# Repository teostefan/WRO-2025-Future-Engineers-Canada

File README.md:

# WRO-2025-Future-Engineers-Canada

The following repository contains the code and technical documentation regarding
the robot created by the CarletonU-uOttawa joint team for the 2025 WRO Future
Engineers competition.

## Contents

- [About our Team](https://github.com/teostefan/WRO-2025-Future-Engineers-Canada/blob/main/README.md#about-our-team)
- [Demo Video](https://github.com/teostefan/WRO-2025-Future-Engineers-Canada/blob/main/README.md#demo-video)
- [Software Setup](https://github.com/teostefan/WRO-2025-Future-Engineers-Canada/blob/main/README.md#software-setup)
- [Power and Sensor Management](https://github.com/teostefan/WRO-2025-Future-Engineers-Canada/blob/main/README.md#power-and-sensor-management)
- [Obstacle Management](https://github.com/teostefan/WRO-2025-Future-Engineers-Canada/blob/main/README.md#obstacle-management)
- [Mobility Management](https://github.com/teostefan/WRO-2025-Future-Engineers-Canada/blob/main/README.md#mobility-management)

## About our Team

Oscar Barbieri is a student at the University of Ottawa and is studying software engineering, and Stefan Teodorescu is a student a Carleton University studying aerospace avionics. Last year, Oscar and Stefan participated in the WRO Future Innovators challenge and made it into the international finals in İzmir. This year, both students have decided to participate in the WRO Future Engineers competition as a means to further their knowledge regarding mechatronics and systems programming.

## Demo Video

A demonstration video of our robot performing both challenges can be found in the [```video``` directory](https://github.com/teostefan/WRO-2025-Future-Engineers-Canada/tree/main/video).

## Software Setup

### Compiling and Running the Robot's Firmware (Linux)

To get started, clone the repository and build the firmware using `make`:

```sh
git clone https://github.com/teostefan/WRO-2025-Future-Engineers-Beta.git
cd WRO-2025-Future-Engineers-Beta
make
```

> **Note**: Depending on how your Linux system is configured, an "insufficient
> privileges" error may be thrown on compilation regarding the file
> `kf_matrix_gen.sh`. To solve this, run
> `sudo chmod 777 ./software/kf/kf_matrix_gen.sh` in the repository's root. If
> this error still persists, use `sudo` in front of `make` as your user might
> not have enough privileges to execute the above bash file.

Then, simply run the `main` executable in the generated `builds` folder:

```sh
builds/main
```

### Compiling and Running Individual Tests

To generate the test executables, run:

```sh
make all-tests
```

Afterwards, all tests will be in the `builds` folder and have a name in the
format `test_xx`. Each test can then be individually executed as in the
following example:

```sh
builds/test_cv
```

### Software Dependencies

If running on Linux, all of the below dependencies should be pre-installed.

- `ffmpeg` - Abstraction layer for the driver, also used for applying filters to
  the video feed.
- `v4l2` - Video4Linux2 multimedia drivers.
- `ffplay` - Media player GUI for debugging.
- `unistd.h` - The UNIX standard header.

## Power and Sensor Management

||
|:--:|
|*Figure 1: Annotated diagram of the vehicle. Individual components are discussed in the subsequent sections.*|

This section pertains to the electrical engineering aspects of our vehicle. Design choices such as computing platforms, power supplies, sensors and motor controllers are discussed. The majority of peripherals have been purchased as breakout boards, and a custom Raspberry-P "Hat" acts as a distribution box and motor controller. A general block diagram of the robot's electrical systems is provided below.

||
|:--:|
|*Figure 2: Diagram of the vehicle's electrical systems. Schematics regarding the custom Raspberry Pi Hat PCB and 5V converter for the servo are provided in the sections below.*|

### Computing Platform

The main controller for the robot is a Raspberry Pi 4B Single Board Computer (SBC). All processing is done on this platform, and no additional controllers have been used, except for an ATTINY45 that generates Pulse-Width Modulation (PWM) to control the speed on the driving motor. This ensures that the system remains simple and allows for a smaller vehicle, which implies better manoeuvrability. The Raspberry-Pi model 4B was specifically chosen as it has a good amount of processing capabilities for the computer-vision algorithms and does not excessively consume power like the newer model 5 (~2.5A@5V versus 5A@5V).

### Power Supply

The vehicle is powered by a 2Ah lithium-ion battery pack that feeds 7.4V nominal into a 3.4A fixed 5V buck regulator and a variable 2A buck-boost regulator set to approximately 9V. The 5V regulator supplies the Raspberry Pi, while the 9V regulator supplies the driving motor. As the steering servo requires 5V only, the 9V from the motor power supply is stepped down to 5V via a simple LM7805 linear regulator circuit (see Figure 3). Although the 5V could have been supplied from the main 5V regulator, this would have been undesirable as any electrical noise caused by the servomotor could permeate to the Raspberry Pi and cause instabilities. For supplying the sensors which work at 3.3V, the internal regulator on the Raspberry Pi is used.

||
|:--:|
|*Figure 3: Schematic of the LM7805 5V regulator for the steering servo. Production files for this board can be found in the [`pcb/servo_regulator`](https://github.com/teostefan/WRO-2025-Future-Engineers-Canada/tree/main/pcb/servo_regulator) directory.*|

||
|:--:|
|*Figure 4: Rendering of the servo regulator custom PCB in KiCAD.*|

### Sensor and Motor Management

In addition to the camera for obstacle detection, as many sensors as possible have been installed on the robot to simplify the control algorithms and to avoid estimating data. For example, all four sides of the robot have optical Time-of-Flight (ToF) distance sensors, allowing the vehicle not only to determine it's rectilinear position, but also to measure clearances precisely for manoeuvres such as parallel parking. In addition, a gyroscope has been installed which can measure absolute rotation angles of the robot. The gyro sensor is also used in a proportional controller to keep the robot driving straight when required.

All sensors, except for the camera which is connected via USB, are interfaced via a common I²C bus. To prevent conflicts in between sensors which have the same addresses (the 4 ToF sensors), an I²C-controlled multiplexer is used for connecting the main bus to only one sensor at a time.

Also on this main I²C bus is an ATTINY45 which is configured as a slave. It generates PWM signals that are then used to drive the DC driving motor via an H-bridge at varying speeds in forwards or reverse. The steering servomotor is separate and is controlled directly by the Raspberry Pi through PWM.

In order to reduce the number of external components and keep the wiring relatively manageable, a custom Raspberry Pi "Hat" has been designed. It includes connectors for all of the individual peripherals and integrates the driving motor controller as well as the I²C multiplexer. The circuit board was designed in KiCAD and all relevant files can be found in the `pcb/main` directory. See Figure 5 at the end of this page for the main board's schematic, and the green inset in Figure 2 for the main board's block diagram.

#### I²C Peripheral Mapping

**Note:** All I²C peripherals are on I²C channel 1 (GPIO2/SDA & GPIO3/SCL).

| Peripheral | Description | I²C Address | Related Drivers |
| ---------- | ----------- | ----------- | --------------- |
| ESC        | Electronic speed controller for main motor. It is just an ATTNY25/45 programmed with the firmware contained in the `software/esc/esc.ino` C++ file. GPIO23 is also used by the driver to put this peripheral to sleep. | `0x08` | `software/esc` |
| BNO055     | Gyroscope/IMU. By default, the address of this sensor will be `0x29`, but this will interfere with the ToF sensors. To select the alternate address `0x28`, pull the `ADC` pin on the breakout board low. | `0x28` | `software/gyro` |
| VL53L0X    | One of four laser ToF sensors. As all sensors have the same address, they must be selected via the I²C switch (see next row). | `0x29` | `software/tof` |
| TCA9544    | 4 Channel I²C switch / multiplexer for selecting 1 of 4 VL53L0X sensors. | `0x70` | `software/i2cmux` |

#### Non-I²C Peripheral Mapping

|   Peripheral   | Description | Pin number & GPIO | Related Drivers |
| -------------- | ----------- | ----------- | --------------- |
| SG-5010        | Standard RC PWM-controlled servo for steering. | `GPIO13/PIN33/PWM1` | `software/esc` |
| KANO Webcam    | Gooseneck USB Camera for computer vision.   | `USB` | `software/cv` |

||
|:--:|
|*Figure 5: Schematic of the main board. Production files for this board can be found in the [`pcb/main`](https://github.com/teostefan/WRO-2025-Future-Engineers-Canada/tree/main/pcb/main) directory.*|

||
|:--:|
|*Figure 6: Rendering of the main board custom PCB in KiCAD.*|

### Bills of Materials

A general Bill of Materials that includes the hardware components as well as the off-the shelf parts can be found at the end of this page. If one desires to fabricate the main board and the servo regulator board, the component-level BOMs can be found in [`pcb/main/main.csv`](https://github.com/teostefan/WRO-2025-Future-Engineers-Canada/tree/main/pcb/main/main.csv) and [`pcb/servo_regulator/servo_regulator.csv`](https://github.com/teostefan/WRO-2025-Future-Engineers-Canada/tree/main/pcb/servo_regulator/servo_regulator.csv).

### Issues faced regarding the sensors

A recurring issue faced during the development of the robot was the instability of the VL53L0X laser time-of-flight sensors (ToF sensors). Despite the [datasheet](https://www.st.com/resource/en/datasheet/vl53l0x.pdf) stating that the performance of the sensor was independent from surface properties, we noticed a very large change in behaviour from when the robot was tested on a black mat versus a glossy white mat like the one used in during the competition. When the ground was highly reflective, the robot would randomly detect walls and behave erratically (see videos below). This occurred whether or not the lights were turned on, suggesting an issue with the sensor's own laser rather than with the ambient light. The effect was also partially corroborated by a [forum post](https://community.st.com/t5/imaging-sensors/vl53l0x-distance-reading-varies-with-reflectivity/td-p/226904) on the manufacturer's website.

<https://github.com/user-attachments/assets/d4aabfce-8ad7-4a68-8b8d-6be23073b4cf>

<https://github.com/user-attachments/assets/641f2a84-3ea8-4779-814c-0cd47e98a4df>

The solution to this issue was to simply have the ToF sensors tilted upwards by 10 degrees with some special 3D printed washers:

|||
|:--:|:--:|
|*Figure 7A: Tilt washers for the front ToF sensor.*|*Figure 7B: Tilt washers for the lateral ToF sensors.*|

This most likely reduced any reflections of the floor coased by the ToF laser's scattering.

## Obstacle Management

For autonomous obstacle avoidance capabilities, the vehicle uses Computer Vision (CV). All software in the vehicle has been written in C, and no premade CV library is used by our code (such as OpenCV). Everything has been written from scratch as a learning experience and to reduce bloat. More details regarding the robot's algorithms is provided below.

### General Algorithm

The following flowchart showcases the robot's behaviour:

||
|:--:|
|*Figure 8: Flowchart of the robot's software.*|

The open challenge uses the lateral ToF sensors to detect when one of the track sides gives way, indicating the direction in which it should turn. For the obstacle challenge, the computer vision algorithm determines the position of the obstacles for the first round, and then stores all positions into an "evidence map". For the next three rounds, the robot can proceed faster as it uses the stored obstacle position instead of recomputing it from camera data every time.

### Computer Vision

In order to detect and avoid obstacles, the robot centres itself at the beginning of each straight section on the mat to determine the obstacles in it's path. It grabs a frame from the camera, and processes it to figure out the positioning and colour of the obstacles/signs.

||
|:--:|
|*Figure 9: Algorithm for the robot's Computer Vision. Relevant code can be found in [```software/cv```](https://github.com/teostefan/WRO-2025-Future-Engineers-Canada/tree/main/software/cv). Obstacle image credit: [WRO Association](https://world-robot-olympiad-association.github.io/future-engineers-gs/p04-cv/).*|

FFMpeg is used as a wrapper for the V4L linux webcam driver to interface with the USB camera and to perform the Gaussian blurring of the image for removing optical noise. The result's pixel data is then piped and stored in a C static array for further processing. Contrast is increased by multiplying each RGB value by 1.5 and then brightness is decreased by subtracting 0.2 from all pixels. This allows bright colours to stand out more and mute fainter colours. Afterwards, the image data is converted from reed-green-blue (RGB) to hue-saturation-luminosity (HSL). A [recursive flood-fill algorithm](https://en.wikipedia.org/wiki/Flood_fill) then subdivides the image into coloured regions by hue, whilst rejecting low saturation and high luminosity regions. While the flood fill algorithm is performed, an accumulator stores the minimum and maximum x and y values for each coloured region to form bounding boxes. Bounding boxes with a minimum dimension less than a threshold are rejected, and the centroids of the remaining bounding boxes are computed. Due to perspective, the y-position of these bounding boxes are used to determine which coloured obstacle is nearer to the robot.

||
|:--:|
|*Figure 10: A simple animation of the flood fill algorithm. Like coloured connected pixels are traversed to find the minimum and maximum values in x and y of the region. Animation credit: [Wikimedia Commons](https://en.wikipedia.org/wiki/File:Recursive_Flood_Fill_4_(aka).gif)*|

### Obstacle Avoidance

Based on the above Computer Vision algorithm, there are four possible cases returned:

|Case|Obstacle Positioning|
|:--:|:--:|
| 1  | Single RED obstacle |
| 2  | Single GREEN obstacle |
| 3  | RED closer, GREEN further |
| 4  | GREEN closer, RED further |

The exact x positioning of these obstacles is not considered, as the possible x-variation is very small (20cm). Based on these four cases, the robot then chooses one of four paths:

|Case|Diagram of the path taken for the detected obstacle configuration|
|:--:|:--:|
| 1  |  |
| 2  |  |
| 3  |  |
| 4  |  |

## Mobility Management

The robot and it's linkages/driveshafts are almost fully 3D printed, with only the differential gear being bought off the shelf. All of it's mechanical components were fully designed in IronCAD. This section provides an overview on the decisions regarding the robot's mobility and construction. To see a more in depth overview of the assembly, skip to the [Assembly Instructions](https://github.com/teostefan/WRO-2025-Future-Engineers-Canada/wiki/Mobility-Management#assembly-instructions-and-boms) section on this page.

### Mechanical Design

For mobility, our vehicle uses a rear wheel drive along with front wheel steering. Keeping the steering wheelset separate from the driving wheelset reduces mechanical complexities and removes the need for universal joints in the drive shafts. The powered rear-wheels are connected to the motor via a ring and pinion differential that allows the individual wheel speeds to vary so long as their average is equal to the speed provided by the driving motor. This allows the vehicle to steer efficiently with minimum wheel slippage on the ground. All rotating shafts are connected to the frame through ball-bearings to minimise friction and wear.

||
|:--:|
|*Figure 11: Diagram of the vehicle's drivetrain, as seen from the bottom. For an exploded view of all the components, see the vehicle construction section below.*|

### Motors

A brushed Mabuchi RK-370CA-15370 direct-current (DC) motor was chosen for the driving motor as it is easier to control than a brushless motor, requiring only a simple H-bridge circuit instead of a three-phase inverter. The motor's power is regulated through pulse-width modulation.

### Vehicle Construction

The chassis is fully 3D-printed, with files available in the [`hardware` directory](https://github.com/teostefan/WRO-2025-Future-Engineers-Canada/tree/main/hardware) at the root of this repository. The front steering and rear driving are implemented as two separate assemblies which are built individually and then attached together via two beams, forming the structure. The Raspberry-Pi 4 is then screwed into the back and the custom PCB is attached on the 40-pin header. A plate supporting all of the regulators is screwed into the back, while breakout boards for the ToF sensors are attached into the side of the chassis through 20 mm M3 brass standoffs. The front ToF sensor is attached with a special 3D printed bracket that also holds the IMU/Gyroscope breakout. A rack in-between the Raspberry-Pi and the steering motor holds the 2 Ah lithium-ion batteries.

||||
|:--:|:--:|:--:|
|*Figure 12A: Front view of the vehicle.*|*Figure 12B: Side view of the vehicle.*|*Figure 12C: Rear view of the vehicle. See the `v-photos` directory for all six views.*|

### Assembly Instructions and BOMs

A detailed PDF assembly manual has been provided for reference alongside with a BOM for all of the hardware components. Some parts in the BOM must be purchased, while others are to be 3D printed. All 3D printed parts have been made in black Bambu Lab PLA. A seperate BOM for the two custom PCBs are provided in [`pcb/main/main.csv`](https://github.com/teostefan/WRO-2025-Future-Engineers-Canada/tree/main/pcb/main/main.csv) and [`pcb/servo_regulator/servo_regulator.csv`](https://github.com/teostefan/WRO-2025-Future-Engineers-Canada/tree/main/pcb/servo_regulator/servo_regulator.csv).

A preview of the BOM and assembly manual is provided below. For better viewing and to zoom-in, please download the [pdf](https://github.com/teostefan/WRO-2025-Future-Engineers-Canada/blob/main/hardware/Assembly_Manual_and_BOM.pdf).

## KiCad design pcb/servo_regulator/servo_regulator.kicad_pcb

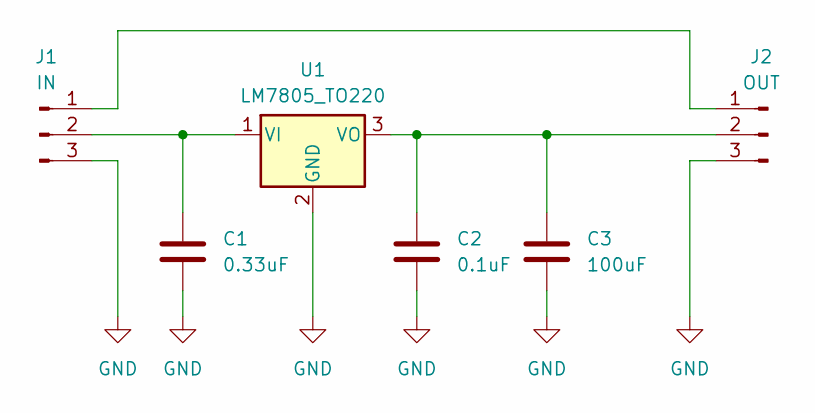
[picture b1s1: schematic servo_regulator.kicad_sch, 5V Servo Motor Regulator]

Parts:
C1: 0.33uF; C_Disc_D4.7mm_W2.5mm_P5.00mm
C2: 0.1uF; C_Disc_D4.7mm_W2.5mm_P5.00mm
C3: 100uF; C_Radial_D5.0mm_H5.0mm_P2.00mm
J1: IN; PinHeader_1x03_P2.54mm_Vertical
J2: OUT; PinHeader_1x03_P2.54mm_Vertical
U1: LM7805_TO220; TO-220-3_Vertical

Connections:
GND: C1.2, C2.2, C3.2, J1.3, J2.3, U1.2 (GND)
unnamed: J1.1, J2.1
unnamed: C1.1, J1.2, U1.1 (VI)
unnamed: C2.1, C3.1, J2.2, U1.3 (VO)

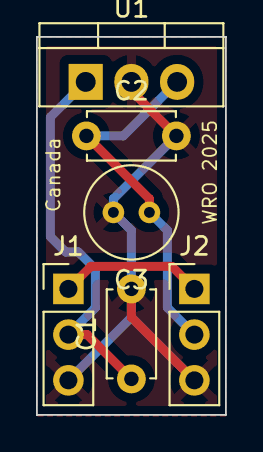
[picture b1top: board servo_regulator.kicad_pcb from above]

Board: 2 copper layers, 10.5 x 21.0 mm, 6 parts (0 on the bottom side), 4 nets.

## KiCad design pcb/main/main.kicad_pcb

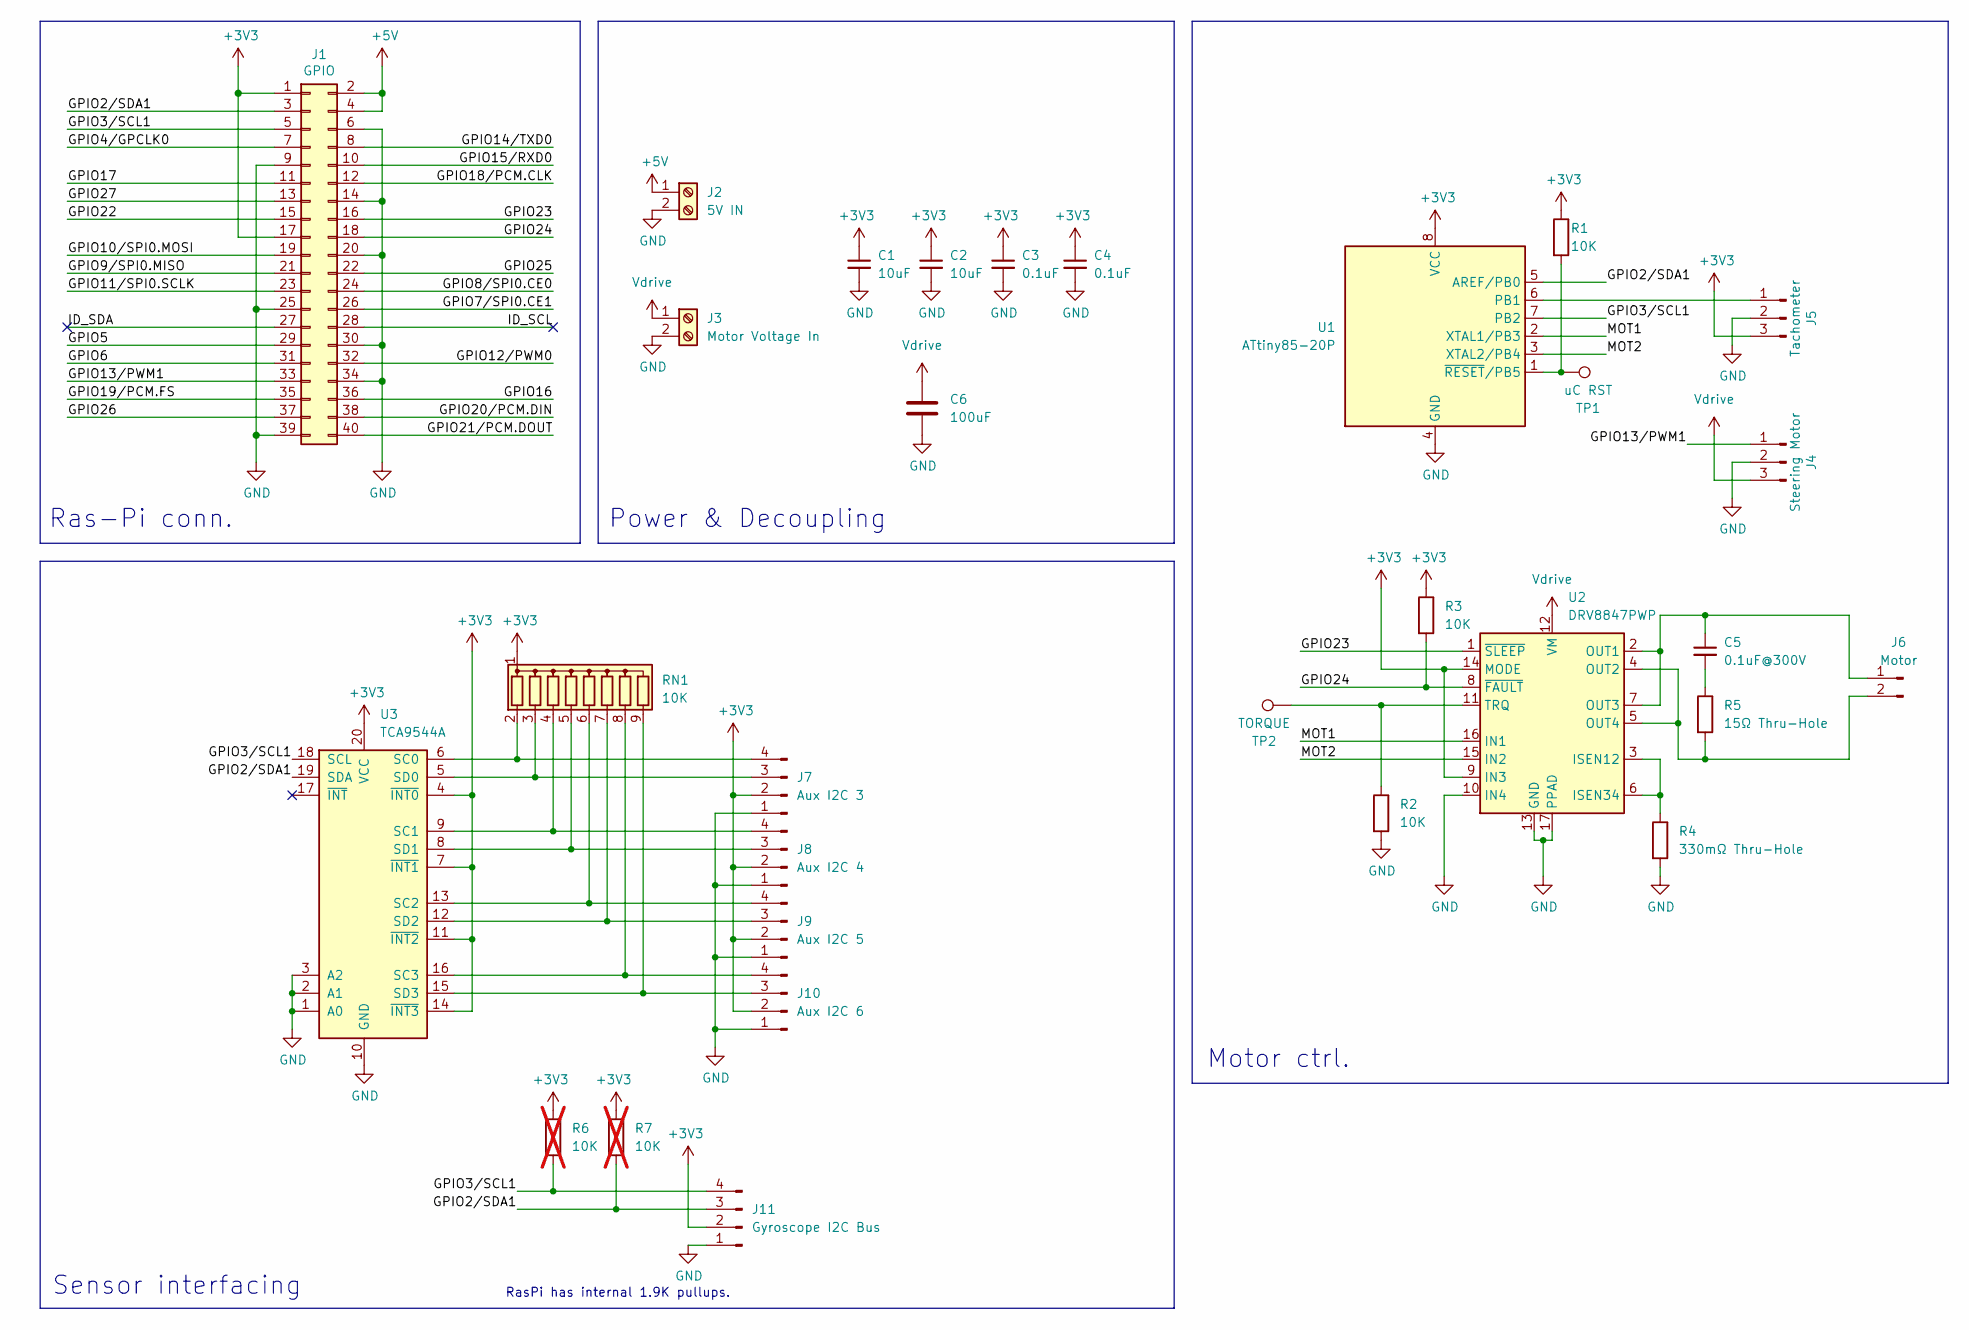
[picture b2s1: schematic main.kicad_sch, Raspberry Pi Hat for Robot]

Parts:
C1, C2: 10uF; C_0603_1608Metric
C3, C4: 0.1uF; C_0603_1608Metric
C5: 0.1uF@300V; C_Disc_D7.5mm_W2.5mm_P5.00mm
C6: 100uF; C_Radial_D5.0mm_H5.0mm_P2.00mm
J1: GPIO; PinSocket_2x20_P2.54mm_Vertical
J2: 5V IN; TerminalBlock_Phoenix_MKDS-1,5-2_1x02_P5.00mm_Horizontal
J3: Motor Voltage In; TerminalBlock_Phoenix_MKDS-1,5-2_1x02_P5.00mm_Horizontal
J4: Steering Motor; PinHeader_1x03_P2.54mm_Vertical
J5: Tachometer; PinHeader_1x03_P2.54mm_Vertical
J6: Motor; JST_PH_B2B-PH-K_1x02_P2.00mm_Vertical
J7: Aux I2C 3; PinHeader_1x04_P2.54mm_Vertical
J8: Aux I2C 4; PinHeader_1x04_P2.54mm_Vertical
J9: Aux I2C 5; PinHeader_1x04_P2.54mm_Vertical
J10: Aux I2C 6; PinHeader_1x04_P2.54mm_Vertical
J11: Gyroscope I2C Bus; PinHeader_1x04_P2.54mm_Vertical
R1, R2, R3: 10K; R_0603_1608Metric
R4: 330mΩ Thru-Hole; R_Axial_DIN0309_L9.0mm_D3.2mm_P2.54mm_Vertical
R5: 15Ω Thru-Hole; R_Axial_DIN0309_L9.0mm_D3.2mm_P2.54mm_Vertical
R6, R7: 10K; R_0603_1608Metric; not fitted
RN1: 10K; R_Array_SIP9
TP1: uC RST; TestPoint_Pad_2.0x2.0mm
TP2: TORQUE; TestPoint_Pad_2.0x2.0mm
U1: ATtiny85-20P; DIP-8_W7.62mm_Socket
U2: DRV8847PWP; HTSSOP-16-1EP_4.4x5mm_P0.65mm_EP3.4x5mm_Mask2.46x2.31mm_The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
U3: TCA9544A; TSSOP-20_4.4x6.5mm_P0.65mm

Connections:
+3V3: C1.1, C2.1, C3.1, C4.1, J1.1, J1.17, J5.3, J7.2, J8.2, J9.2, J10.2, J11.2, R1.1, R3.1, R6.1, R7.1, RN1.1 (common), U1.8 (VCC), U2.9 (IN3), U2.14 (MODE), U3.4 (~INT0), U3.7 (~INT1), U3.11 (~INT2), U3.14 (~INT3), U3.20 (VCC)
+5V: J1.2, J1.4, J2.1
/GPIO2/SDA1: J1.3, J11.3, R7.2, U1.5 (AREF/PB0), U3.19 (SDA)
/GPIO3/SCL1: J1.5, J11.4, R6.2, U1.7 (PB2), U3.18 (SCL)
/GPIO4/GPCLK0: J1.7
/GPIO5: J1.29
/GPIO6: J1.31
/GPIO7/SPI0.CE1: J1.26
/GPIO8/SPI0.CE0: J1.24
/GPIO9/SPI0.MISO: J1.21
/GPIO10/SPI0.MOSI: J1.19
/GPIO11/SPI0.SCLK: J1.23
/GPIO12/PWM0: J1.32
/GPIO13/PWM1: J1.33, J4.1
/GPIO14/TXD0: J1.8
/GPIO15/RXD0: J1.10
/GPIO16: J1.36
/GPIO17: J1.11
/GPIO18/PCM.CLK: J1.12
/GPIO19/PCM.FS: J1.35
/GPIO20/PCM.DIN: J1.38
/GPIO21/PCM.DOUT: J1.40
/GPIO22: J1.15
/GPIO23: J1.16, U2.1 (~SLEEP)
/GPIO24: J1.18, R3.2, U2.8 (~FAULT)
/GPIO25: J1.22
/GPIO26: J1.37
/GPIO27: J1.13
/ID_SCL: J1.28
/ID_SDA: J1.27
/MOT1: U1.2 (XTAL1/PB3), U2.16 (IN1)
/MOT2: U1.3 (XTAL2/PB4), U2.15 (IN2)
GND: C1.2, C2.2, C3.2, C4.2, C6.2, J1.6, J1.9, J1.14, J1.20, J1.25, J1.30, J1.34, J1.39, J2.2, J3.2, J4.2, J5.2, J7.1, J8.1, J9.1, J10.1, J11.1, R2.2, R4.2, U1.4 (GND), U2.10 (IN4), U2.13 (GND), U2.17 (PPAD), U3.1 (A0), U3.2 (A1), U3.3 (A2), U3.10 (GND)
unnamed: C5.2, R5.1
unnamed: J5.1, U1.6 (PB1)
unnamed: C5.1, J6.1, U2.2 (OUT1), U2.7 (OUT3)
unnamed: J6.2, R5.2, U2.4 (OUT2), U2.5 (OUT4)
unnamed: J7.3, RN1.3 (R2), U3.5 (SD0)
unnamed: J7.4, RN1.2 (R1), U3.6 (SC0)
unnamed: J8.3, RN1.5 (R4), U3.8 (SD1)
unnamed: J8.4, RN1.4 (R3), U3.9 (SC1)
unnamed: J9.3, RN1.7 (R6), U3.12 (SD2)
unnamed: J9.4, RN1.6 (R5), U3.13 (SC2)
unnamed: J10.3, RN1.9 (R8), U3.15 (SD3)
unnamed: J10.4, RN1.8 (R7), U3.16 (SC3)
unnamed: R1.2, TP1.1, U1.1 (~RESET/PB5)
unnamed: R4.1, U2.3 (ISEN12), U2.6 (ISEN34)
unnamed: R2.1, TP2.1, U2.11 (TRQ)
Vdrive: C6.1, J3.1, J4.3, U2.12 (VM)

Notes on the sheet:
Motor ctrl.
Sensor interfacing
Ras-Pi conn.
RasPi has internal 1.9K pullups.
Power & Decoupling

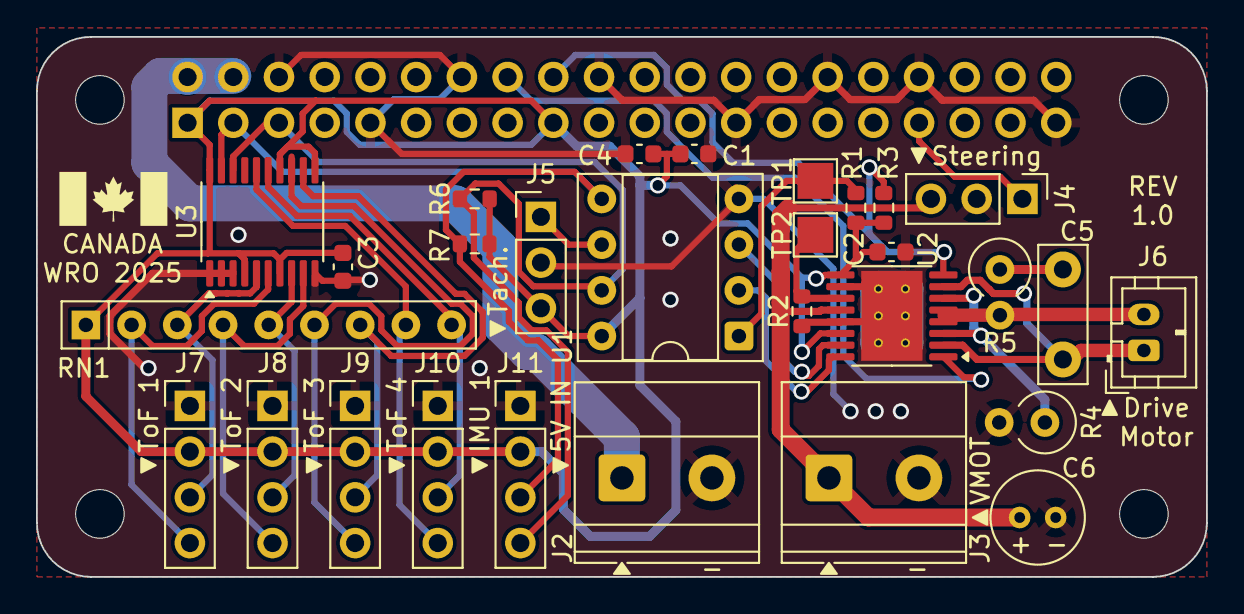
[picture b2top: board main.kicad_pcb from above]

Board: 2 copper layers, 65.0 x 30.0 mm, 34 parts (1 on the bottom side), 26 nets.

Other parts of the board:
MH1, MH2, MH3, MH4: MountingHole_2.7mm_M2.5

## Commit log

2025-07-29 Relocated BNO055 module
2025-07-30 Renamed the BNO055 directory to "gyro" for more consistency
2025-08-03 Fixed Makefile
2025-08-03 Testing updates to gyro and tof
2025-08-03 Relocated io.c and deleted io.h
2025-08-03 Created tof module
2025-08-03 Fix compilation errors
2025-08-04 Added test_tof.c program
2025-08-04 Created i2c mux driver; all ToF sensors tested good.
2025-08-04 Added drivers to interface with the ESC and changed error messages in i2cmux.
2025-08-04 Update CV to contain accurate obstacle colours
2025-08-04 Add ESC enable/disable function for H-Bridge and implement steering servo control.
2025-08-05 Fixed CV
2025-08-05 Tested BNO055
2025-08-06 Fix all motor related issues; all functions have been successfully tested.
2025-08-06 Fixed firmware issues in the ATTINY45 microcontroller that resulted in I²C bus desynchronisation by using hardware PWM peripherals instead of emulating PWM through software.
2025-08-06 Added comment to clarify possible pigpio "errors" given by the linter in esc.h
2025-08-07 Added polling routine for starting the main program
2025-08-13 Fixed CV, but better
2025-08-13 Another test_cv update
2025-08-14 Created IO module
2025-08-16 fix makefile and globals
2025-08-23 push everything in case it crashes again
2025-08-24 Add media folder
2025-08-24 Update drivetrain diagram in media
2025-08-24 first lap procedures and smoke test
2025-08-24 Add PCB manufacturing files and 3D renders of the PCB
2025-08-24 Add PCB BOM
2025-08-26 fixed compilation errors.
2025-08-29 Got the button working
2025-08-29 Added main board schematic in media folder
2025-08-29 Fixed time loss issue with CV
2025-08-30 drives three laps with reverse
2025-08-30 Turn around, red-red, green-green
2025-08-31 obstacle tight left, obstacle tight right
2025-08-31 pull out from the left, pull out from the right, pp on the right
2025-08-31 parallel park on the left side
2025-09-01 Added electrical diagram
2025-09-01 Added SVG version of the drivetrain diagram
2025-09-01 Added PCB files for the robot
2025-09-01 Updated schematic images
2025-09-01 push all changes
2025-09-01 Added BOM for the servo regulator
2025-09-03 Drive around obstacles
2025-09-05 new cv
2025-09-05 bring non-cv related changes from new-cv
2025-09-06 Create hardware directory
2025-09-06 Added CAD file for the whole vehicle
2025-09-06 Added Assembly Manual and BOM PDF
2025-09-06 Renamed instruction manual to assembly manual for clarity
2025-09-06 Updated README.md in hardware directory
2025-09-06 Added PDF previews for the assembly manual and BOM
2025-09-06 Added sensor diagram into media
2025-09-06 Added robot images 1/2
2025-09-06 Added robot images 2/2
2025-09-07 working open challenge
2025-09-07 refine open challenge
2025-09-07 Added rendering of the servo regulator PCB
2025-09-07 Added computer vision diagram
2025-09-07 Added recursive flood-fill animation
2025-09-07 Added trajectory diagrams to media
2025-09-07 Added corrected trajectory diagrams to media
2025-09-07 Added corrected obstacle avoidance diagrams
2025-09-07 Added videos to media showcasing ToF sensor issues
2025-09-07 Added tilt washer images to media
2025-09-07 Added algorithm flowchart in media
2025-09-08 Update repository format
2025-09-08 changes from testing
2025-09-08 Added robot video
2025-09-08 final push before submit
2025-09-08 Update manoeuvres.c to account for name change of function
2025-09-09 prepared final test
2025-09-09 executed manoeuvre tests
2025-09-10 Perfected CV
2025-09-11 Does 3 laps avoiding obstacles
2025-09-11 better precision and pull out
2025-09-11 adjust first lap logic
2025-09-12 sae before quitting
2025-09-12 pulls out and does 3 laps
2025-09-13 parallel parking and leds

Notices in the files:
pcb/main/main.kicad_pcb:
© 2025 Stefan Teodorescu
pcb/main/main.kicad_sch:
© 2025 Stefan Teodorescu and Oscar Barbieri
pcb/servo_regulator/servo_regulator.kicad_pcb:
© 2025 Stefan
